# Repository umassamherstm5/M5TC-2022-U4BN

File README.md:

# M5TC-2022-U4BN
M5TC board that uses button inputs to display binary, decimal, and hexadecimal representations of unsigned 4-bit numbers.

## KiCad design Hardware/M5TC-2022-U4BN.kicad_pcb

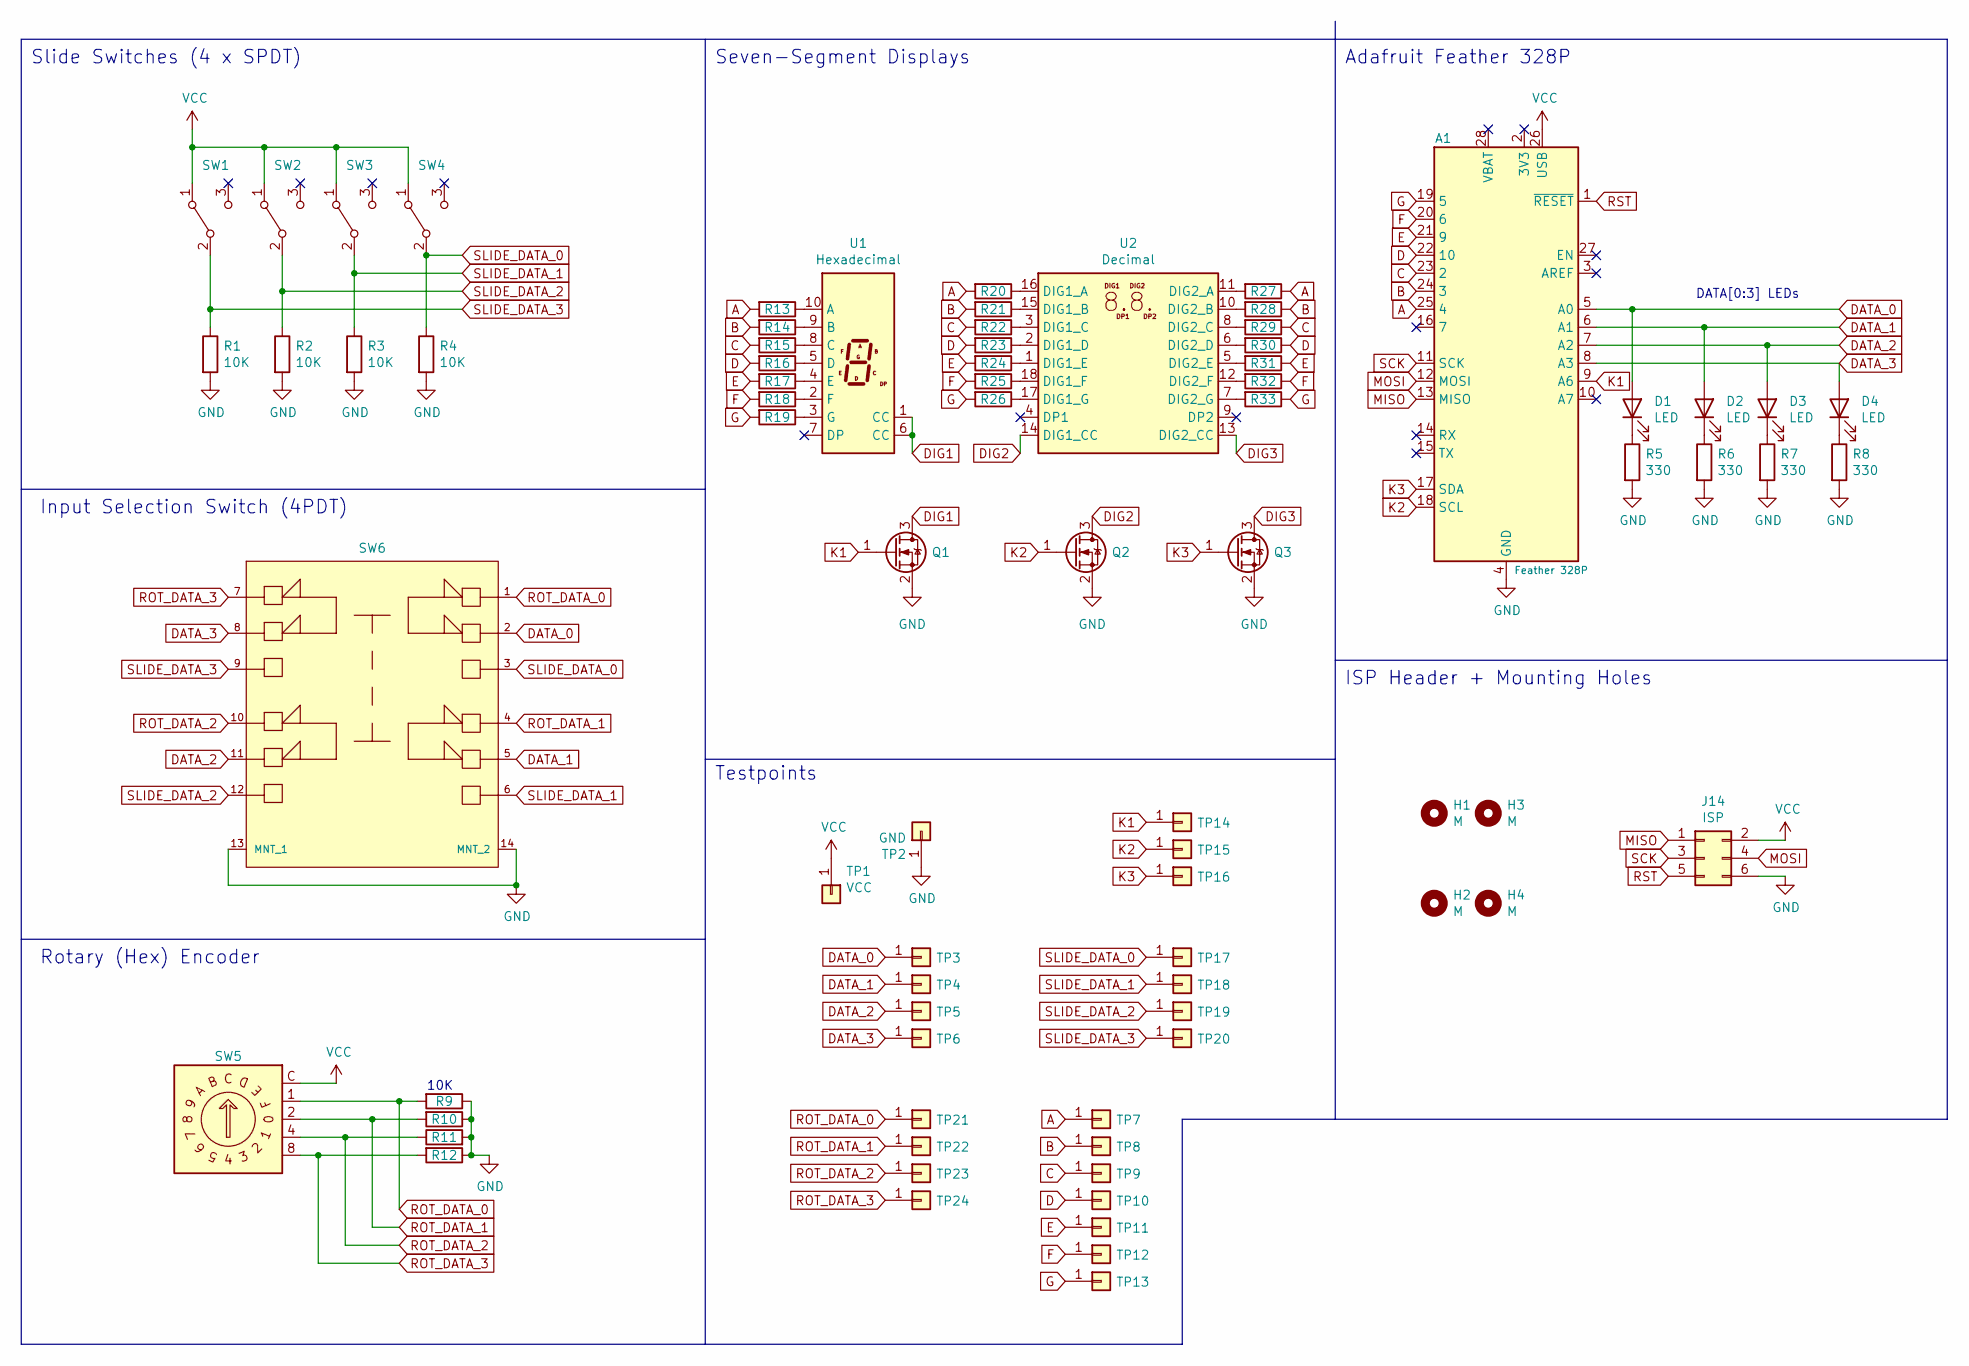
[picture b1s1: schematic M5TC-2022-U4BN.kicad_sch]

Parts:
A1: Feather 328P; Adafruit_Feather
D1, D2, D3, D4: LED; LED_D5.0mm
H1, H2, H3, H4: M; MountingHole_5.3mm_M5_Pad_Via
J14: ISP; PinSocket_2x03_P2.54mm_Vertical
Q1, Q2, Q3: 2N7002; SOT-23
R1, R2, R3, R4, R9, R10, R11, R12: 10K; R_1206_3216Metric
R5, R6, R7, R8, R13, R14, R15, R16, R17, R18, R19, R20, R21, R22, R23, R24, R25, R26, R27, R28, R29, R30, R31, R32, R33: 330; R_1206_3216Metric
SW1, SW2, SW3, SW4: SW_SPDT; E-Switch-EG1218
SW5: SW_Coded_SH-7050; Rotary_Hex_6_SOIC
SW6: EG4208A; E-Switch-EG4208A-0-0-MFG; mouser part number 612-EG4208A; digikey description SWITCH SLIDE 4PDT 200MA 30V
TP1: VCC; TestPoint_LoopPostPad
TP2: GND; TestPoint_LoopPostPad
TP3: DATA_0; TestPoint_LoopPostPad
TP4: DATA_1; TestPoint_LoopPostPad
TP5: DATA_2; TestPoint_LoopPostPad
TP6: DATA_3; TestPoint_LoopPostPad
TP7, TP8, TP9, TP10, TP11, TP12, TP13: Conn_01x01; TestPoint_LoopPost
TP14: K1; TestPoint_LoopPostPad
TP15: K2; TestPoint_LoopPostPad
TP16: K3; TestPoint_LoopPostPad
TP17: SLIDE_DATA_0; TestPoint_LoopPostPad
TP18: SLIDE_DATA_1; TestPoint_LoopPostPad
TP19: SLIDE_DATA_2; TestPoint_LoopPostPad
TP20: SLIDE_DATA_3; TestPoint_LoopPostPad
TP21: ROT_DATA_0; TestPoint_LoopPostPad
TP22: ROT_DATA_1; TestPoint_LoopPostPad
TP23: ROT_DATA_2; TestPoint_LoopPostPad
TP24: ROT_DATA_3; TestPoint_LoopPostPad
U1: Hexadecimal; HDSP-A151
U2: Decimal; DA56-11SURKWA

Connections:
A: A1.25 (4), R13.2, R20.2, R27.1, TP7.1
B: A1.24 (3), R14.2, R21.2, R28.1, TP8.1
C: A1.23 (2), R15.2, R22.2, R29.1, TP9.1
D: A1.22 (10), R16.2, R23.2, R30.1, TP10.1
DATA_0: A1.5 (A0), D1.2 (A), SW6.2, TP3.1
DATA_1: A1.6 (A1), D2.2 (A), SW6.5, TP4.1
DATA_2: A1.7 (A2), D3.2 (A), SW6.11, TP5.1
DATA_3: A1.8 (A3), D4.2 (A), SW6.8, TP6.1
DIG1: Q1.3 (D), U1.1 (CC), U1.6 (CC)
DIG2: Q2.3 (D), U2.14 (DIG1_CC)
DIG3: Q3.3 (D), U2.13 (DIG2_CC)
E: A1.21 (9), R17.2, R24.2, R31.1, TP11.1
F: A1.20 (6), R18.2, R25.2, R32.1, TP12.1
G: A1.19 (5), R19.2, R26.2, R33.1, TP13.1
GND: A1.4 (GND), J14.6, Q1.2 (S), Q2.2 (S), Q3.2 (S), R1.2, R2.2, R3.2, R4.2, R5.2, R6.2, R7.2, R8.2, R9.1, R10.1, R11.2, R12.1, SW6.13 (MNT_1), SW6.14 (MNT_2), TP2.1
K1: A1.9 (A6), Q1.1 (G), TP14.1
K2: A1.18 (SCL), Q2.1 (G), TP15.1
K3: A1.17 (SDA), Q3.1 (G), TP16.1
MISO: A1.13 (MISO), J14.1
MOSI: A1.12 (MOSI), J14.4
unnamed: D1.1 (K), R5.1
unnamed: D2.1 (K), R6.1
unnamed: D3.1 (K), R7.1
unnamed: D4.1 (K), R8.1
unnamed: R13.1, U1.10 (A)
unnamed: R14.1, U1.9 (B)
unnamed: R15.1, U1.8 (C)
unnamed: R16.1, U1.5 (D)
unnamed: R17.1, U1.4 (E)
unnamed: R18.1, U1.2 (F)
unnamed: R19.1, U1.3 (G)
unnamed: R20.1, U2.16 (DIG1_A)
unnamed: R21.1, U2.15 (DIG1_B)
unnamed: R22.1, U2.3 (DIG1_C)
unnamed: R23.1, U2.2 (DIG1_D)
unnamed: R24.1, U2.1 (DIG1_E)
unnamed: R25.1, U2.18 (DIG1_F)
unnamed: R26.1, U2.17 (DIG1_G)
unnamed: R27.2, U2.11 (DIG2_A)
unnamed: R28.2, U2.10 (DIG2_B)
unnamed: R29.2, U2.8 (DIG2_C)
unnamed: R30.2, U2.6 (DIG2_D)
unnamed: R31.2, U2.5 (DIG2_E)
unnamed: R32.2, U2.12 (DIG2_F)
unnamed: R33.2, U2.7 (DIG2_G)
ROT_DATA_0: R9.2, SW5.1, SW6.1, TP21.1
ROT_DATA_1: R10.2, SW5.2, SW6.4, TP22.1
ROT_DATA_2: R11.1, SW5.4, SW6.10, TP23.1
ROT_DATA_3: R12.2, SW5.8, SW6.7, TP24.1
RST: A1.1 (~RESET), J14.5
SCK: A1.11 (SCK), J14.3
SLIDE_DATA_0: R4.1, SW4.2 (B), SW6.3, TP17.1
SLIDE_DATA_1: R3.1, SW3.2 (B), SW6.6, TP18.1
SLIDE_DATA_2: R2.1, SW2.2 (B), SW6.12, TP19.1
SLIDE_DATA_3: R1.1, SW1.2 (B), SW6.9, TP20.1
VCC: A1.26 (USB), J14.2, SW1.1 (A), SW2.1 (A), SW3.1 (A), SW4.1 (A), SW5.C, TP1.1

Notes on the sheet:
Seven-Segment Displays
DATA[0:3] LEDs
Adafruit Feather 328P
Rotary (Hex) Encoder
10K
Slide Switches (4 x SPDT)
Input Selection Switch (4PDT)
Testpoints
ISP Header + Mounting Holes

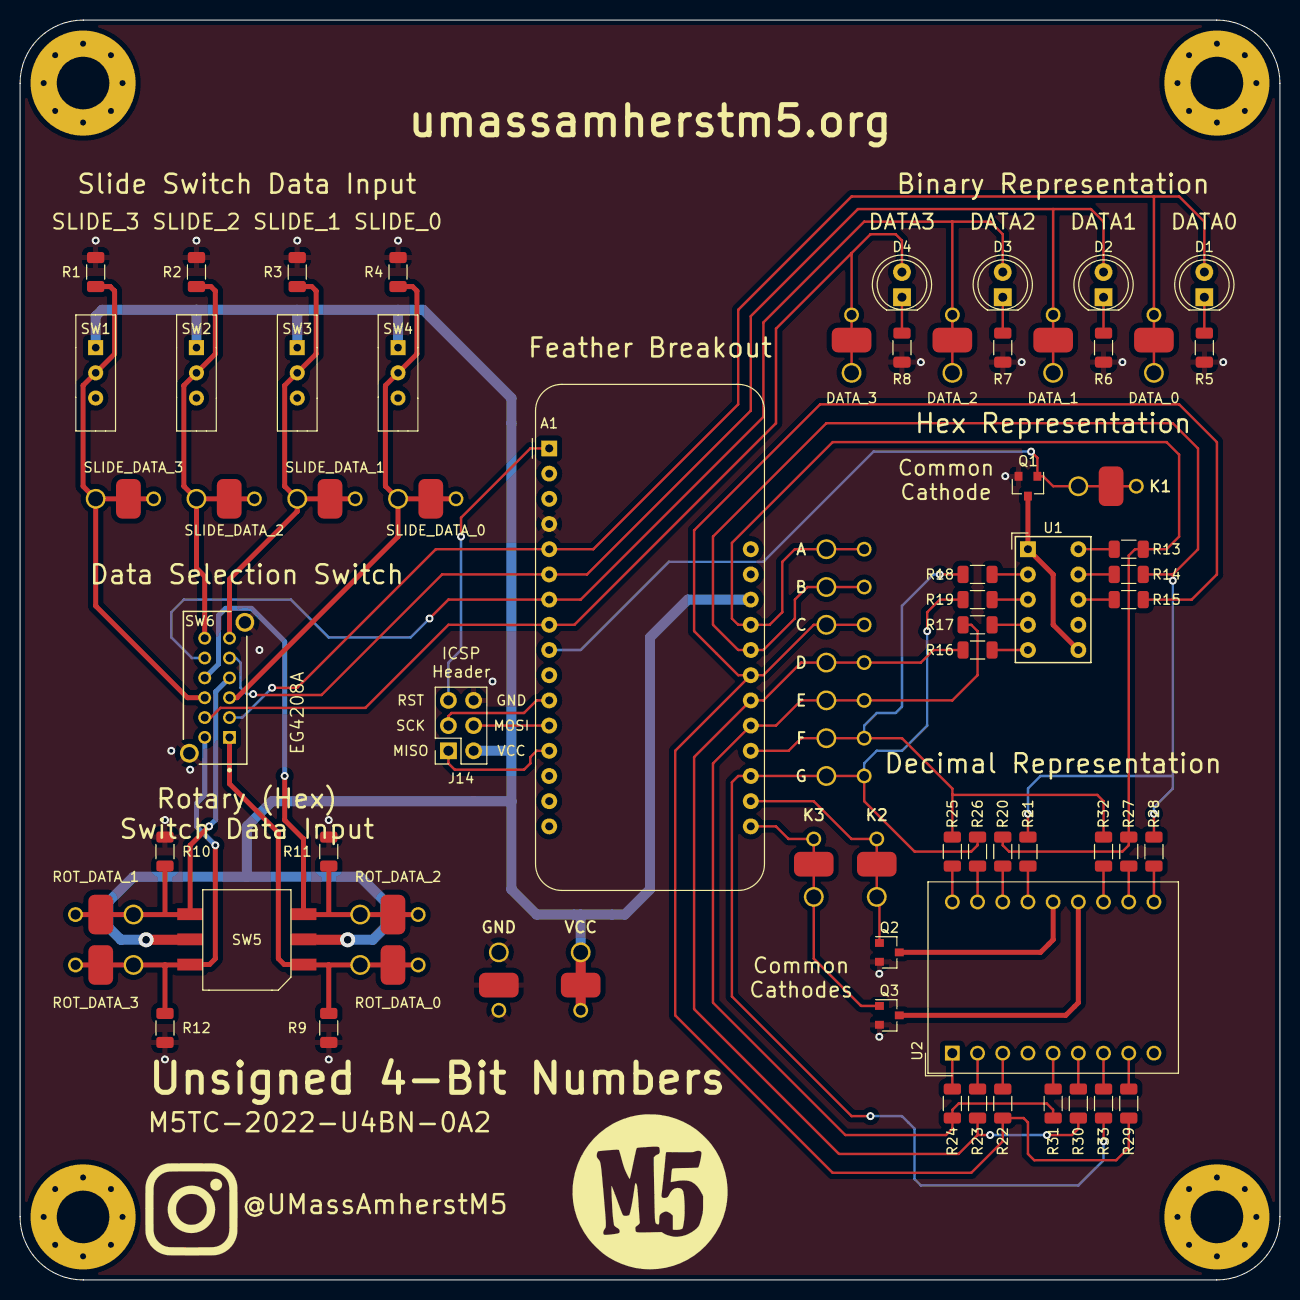
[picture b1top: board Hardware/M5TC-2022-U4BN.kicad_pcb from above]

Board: 2 copper layers, 127.0 x 127.0 mm, 78 parts (0 on the bottom side), 56 nets.

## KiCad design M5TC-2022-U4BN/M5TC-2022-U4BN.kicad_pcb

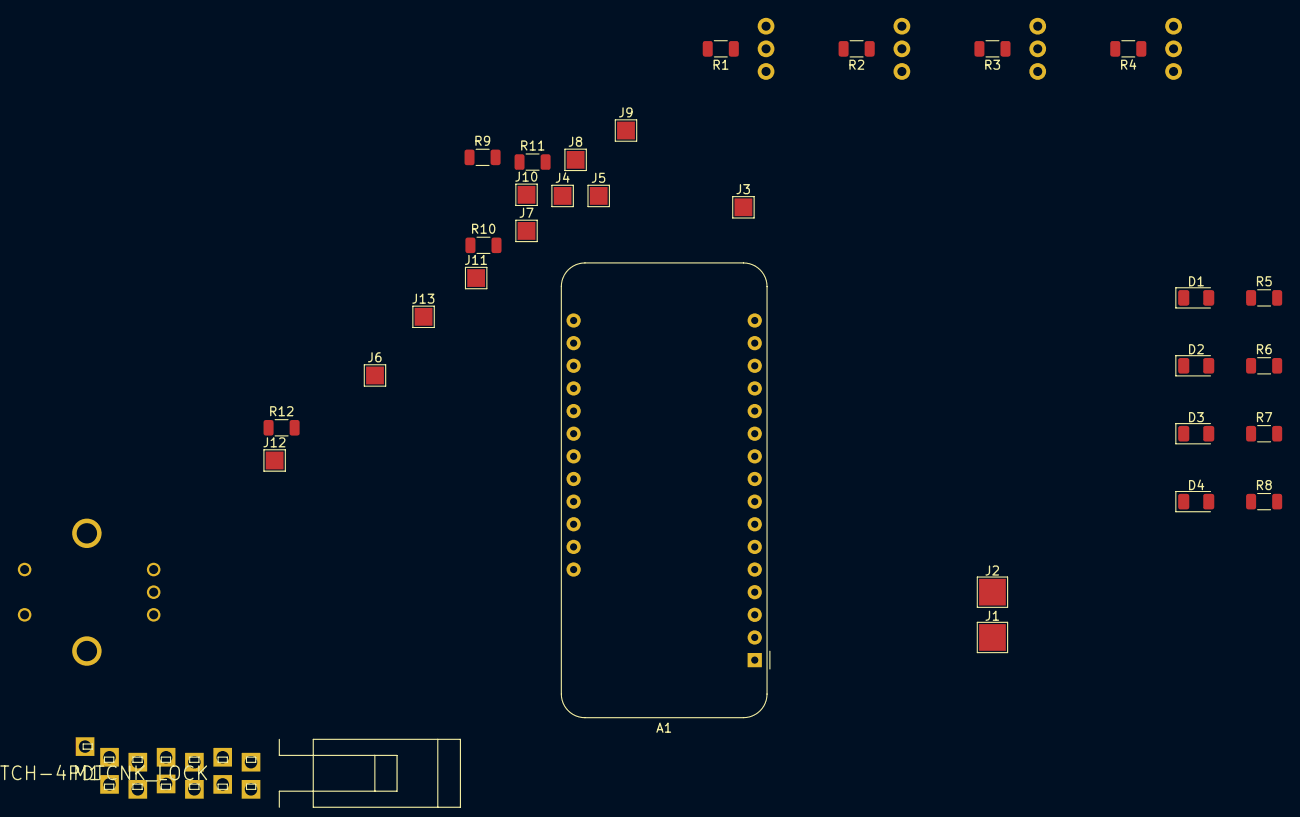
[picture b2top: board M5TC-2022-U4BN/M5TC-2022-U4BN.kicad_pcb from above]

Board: 2 copper layers, 36 parts (0 on the bottom side), 21 nets, no tracks yet.

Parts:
A1: Feather 328P; Adafruit_Feather
D1, D2, D3, D4: LED; LED_1206_3216Metric
J1: VCC; TestPoint_Pad_3.0x3.0mm
J2: GND; TestPoint_Pad_3.0x3.0mm
J3: DATA_0; TestPoint_Pad_2.0x2.0mm
J4: DATA_1; TestPoint_Pad_2.0x2.0mm
J5: DATA_2; TestPoint_Pad_2.0x2.0mm
J6: DATA_3; TestPoint_Pad_2.0x2.0mm
J7: K1; TestPoint_Pad_2.0x2.0mm
J8: K2; TestPoint_Pad_2.0x2.0mm
J9: K3; TestPoint_Pad_2.0x2.0mm
J10: SLIDE_DATA_0; TestPoint_Pad_2.0x2.0mm
J11: SLIDE_DATA_1; TestPoint_Pad_2.0x2.0mm
J12: SLIDE_DATA_2; TestPoint_Pad_2.0x2.0mm
J13: SLIDE_DATA_3; TestPoint_Pad_2.0x2.0mm
M1: SWITCH-4PDTCNK_LOCK; SWITCH-4PDT-CNK
R1, R2, R3, R4: 10K; R_1206_3216Metric
R5, R6, R7, R8: 330; R_1206_3216Metric
R9, R10, R11, R12: R; R_1206_3216Metric
SW1, SW2, SW3, SW4: SW_SPDT; SWITCH-SPDT
SW5: SW_Coded_SH-7050; ROTARY_ENC_PLAIN

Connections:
+5V: A1.26, SW1.1, SW2.1, SW3.1, SW4.1
DATA_0: A1.8, D1.2, J3.1, M1.PP$2
DATA_1: A1.7, D2.2, J4.1, M1.PP$5
DATA_2: A1.6, D3.2, J5.1, M1.PP$8
DATA_3: A1.5, D4.2, J6.1
GND: A1.4, J2.1, R1.2, R2.2, R3.2, R4.2, R5.2, R6.2, R7.2, R8.2, R9.1, R10.1, R11.2, R12.1
K1: A1.11, J7.1
K2: A1.12, J8.1
K3: A1.13, J9.1
unnamed: D1.1, R5.1
unnamed: D2.1, R6.1
unnamed: D3.1, R7.1
unnamed: D4.1, R8.1
ROT_DATA_0: M1.PP$3, R9.2
ROT_DATA_1: M1.PP$6, R10.2
ROT_DATA_2: M1.PP$9, R11.1
SLIDE_DATA_0: J10.1, M1.PP$1, R4.1, SW4.2
SLIDE_DATA_1: J11.1, M1.PP$4, R3.1, SW3.2
SLIDE_DATA_2: J12.1, M1.PP$7, R2.1, SW2.2
SLIDE_DATA_3: J13.1, R1.1, SW1.2
VCC: J1.1, SW5.C

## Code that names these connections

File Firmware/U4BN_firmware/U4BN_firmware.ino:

/*
 * M5TC-U4BN-0A2
 * -------------
 * Displays inputs from SDPT switch/rotary encoder as unsigned 4-bit numbers.
 * Authors: Akshat Sahay, Samridh Tuteja
 */

/*
 * Special Registers: 
 * ------------------
 * This code uses registers on the ATMEGA328P directly using AVR-C. 
 * Good reference: https://exploreembedded.com/wiki/Basics_of_AVR_%27C%27
 * Another good reference: https://www.youtube.com/watch?v=tBq3sO1Z-7o
 * 
 * We use registers directly TODO:{B/C it is better then teh arduino library sine it does not hide how the hardware works}. 
 * 
 * The 328P has 3 port registers: PORTB, PORTC and PORTD. 
 * We access them to get inputs and send outputs using the MCU. 
 * 
 * DDRx:
 * -----
 *  - Stands for Data Direction Register. 
 *  - Determines whether the pins on the specified port are inputs(0) or outputs(1). 
 *  - For example: DDRD = 00001100, here all pins except pins 2 and 3 are inputs on PORTD. 
 *  - Corresponding Arduino function: pinMode(); 
 * 
 * PORTx:
 * ------
 *  - Physical port on the ATMEGA328P. 
 *  - Determines whether the pins on the specified port are set HIGH(5V) or LOW(0V) in our code. 
 *  - For example: PORTB = 01100010, here we set all pins except pins 2, 5 and 6 are LOW. 
 *  - Corresponding Arduino function: digitalWrite(); 
 *  
 * PINx:
 * ------
 *  - Physical port on the ATMEGA328P. 
 *  - Checks the value of pins, either HIGH(5V) or LOW(0V). 
 *  - For example: data_decimal = PINC, here we assign the values of PORTC to the variable data_decimal. 
 *  - Corresponding Arduino function: digitalRead(); 
 */

#define SEG_DELAY_MS 1

#define SEG_A PD4
#define SEG_B PD3
#define SEG_C PD2
#define SEG_D PB2
#define SEG_E PB1
#define SEG_F PD6
#define SEG_G PD5

#define DATA_0 PC0
#define DATA_1 PC1
#define DATA_2 PC2
#define DATA_3 PC3

#define K1 PC6
#define K2 PC4
#define K3 PC5

/* registers variables */
unsigned char num_displayed = 0;  // number displayed on the 7-segment  
unsigned char data_decimal = 0;   // data from PORTC in decimal 
unsigned char data_hex = 0;       // data from PORTC in hex, two digits each 

void setup() {
  // set PORTB and PORTD as OUTPUT 
  DDRB = 0xFF; 
  DDRD = 0xFF; 
  
  // set PORTC as INPUT + K1, K2, K3 as OUTPUT
  DDRC = (0 << K1) | (1 << K2) | (1 << K3);
}

void loop() {
  // get DATA inputs from PORTC, we only want lower 4 bits 
  data_decimal = PINC & 0b00001111; 

  // display output to K1
  number_to_seg(data_decimal);
  
  PORTC |= (1 << K1);
  delay(SEG_DELAY_MS);
  PORTC &= ~(1 << K1);
  clear_seg();

  // display output to K2
  number_to_seg(data_decimal % 10);
  
  PORTC |= (1 << K2);
  delay(SEG_DELAY_MS);
  PORTC &= ~(1 << K2);
  clear_seg();

  // display output to K3
  number_to_seg(data_decimal / 10);
  
  PORTC |= (1 << K3);
  delay(SEG_DELAY_MS);
  PORTC &= ~(1 << K3);
  clear_seg();
}

void clear_seg() {
  PORTB &= ~(1 << SEG_D)|(1 << SEG_E);
  PORTD &= ~(
       (1 << SEG_A)
      |(1 << SEG_B)
      |(1 << SEG_C)
      |(1 << SEG_F)
      |(1 << SEG_G)
  );
}

/* turn on seven-segment signals based on num  */
void number_to_seg(unsigned char num) {
  if (num == 0) {
    // SEG_A ON, SEG_B ON, SEG_C ON, SEG_D ON, SEG_E ON, SEG_F ON, SEG_G OFF
    PORTB = (1 << SEG_D) | (1 << SEG_E); 
    PORTD = (1 << SEG_A) | (1 << SEG_B) | (1 << SEG_C) | (1 << SEG_F); 
  }

  if (num == 1) {
    // SEG_A OFF, SEG_B ON, SEG_C ON, SEG_D OFF, SEG_E OFF, SEG_F OFF, SEG_G OFF
    PORTB = 0x00; 
    PORTD = (1 << SEG_B) | (1 << SEG_C); 
  }

  if (num == 2) {
    // SEG_A ON, SEG_B ON, SEG_C OFF, SEG_D ON, SEG_E ON, SEG_F OFF, SEG_G ON
    PORTB = (1 << SEG_D) | (1 << SEG_E); 
    PORTD = (1 << SEG_A) | (1 << SEG_B) | (1 << SEG_G); 
  }

  if (num == 3) { 
    // SEG_A ON, SEG_B ON, SEG_C ON, SEG_D ON, SEG_E OFF, SEG_F OFF, SEG_G ON
    PORTB = (1 << SEG_D); 
    PORTD = (1 << SEG_A) | (1 << SEG_B) | (1 << SEG_C) | (1 << SEG_G); 
  }

  if (num == 4) {
    // SEG_A OFF, SEG_B ON, SEG_C ON, SEG_D OFF, SEG_E OFF, SEG_F ON, SEG_G ON 
    PORTB = 0x00;
    PORTD = (1 << SEG_B) | (1 << SEG_C) | (1 << SEG_F) | (1 << SEG_G); 
  }

  if (num == 5) {
    // SEG_A ON, SEG_B OFF, SEG_C ON, SEG_D ON, SEG_E OFF, SEG_F ON, SEG_G ON
    PORTB = (1 << SEG_D); 
    PORTD = (1 << SEG_A) | (1 << SEG_C) | (1 << SEG_F) | (1 << SEG_G); 
  }

  if (num == 6) {
    // SEG_A ON, SEG_B OFF, SEG_C ON, SEG_D ON, SEG_E ON, SEG_F ON, SEG_G ON
    PORTB = (1 << SEG_D) | (1 << SEG_E); 
    PORTD = (1 << SEG_A) | (1 << SEG_C) | (1 << SEG_F) | (1 << SEG_G); 
  }

  if (num == 7) {
    // SEG_A ON, SEG_B ON, SEG_C ON, SEG_D OFF, SEG_E OFF, SEG_F OFF, SEG_G OFF
    PORTB = 0; 
    PORTD = (1 << SEG_A) | (1 << SEG_B) | (1 << SEG_C); 
  }

  if (num == 8) {
    // SEG_A ON, SEG_B ON, SEG_C ON, SEG_D ON, SEG_E ON, SEG_F ON, SEG_G ON
    PORTB = (1 << SEG_D) | (1 << SEG_E); 
    PORTD = (1 << SEG_A) | (1 << SEG_B) | (1 << SEG_C) | (1 << SEG_F) | (1 << SEG_G); 
  }

  if (num == 9) {
    // SEG_A ON, SEG_B ON, SEG_C ON, SEG_D ON, SEG_E OFF, SEG_F ON, SEG_G ON
    PORTB = (1 << SEG_D); 
    PORTD = (1 << SEG_A) | (1 << SEG_B) | (1 << SEG_C) | (1 << SEG_F) | (1 << SEG_G); 
  }

  if (num == 10) {
    // SEG_A ON, SEG_B ON, SEG_C ON, SEG_D OFF, SEG_E ON, SEG_F ON, SEG_G ON 
    PORTB = (1 << SEG_E); 
    PORTD = (1 << SEG_A) | (1 << SEG_B) | (1 << SEG_C) | (1 << SEG_F) | (1 << SEG_G); 
  }

  if (num == 11) {
    // SEG_A OFF, SEG_B OFF, SEG_C ON, SEG_D ON, SEG_E ON, SEG_F ON, SEG_G ON
    PORTB = (1 << SEG_D) | (1 << SEG_E); 
    PORTD = (1 << SEG_C) | (1 << SEG_F) | (1 << SEG_G); 
  }

  if (num == 12) {
    // SEG_A ON, SEG_B OFF, SEG_C OFF, SEG_D ON, SEG_E ON, SEG_F ON, SEG_G OFF
    PORTB = (1 << SEG_D) | (1 << SEG_E); 
    PORTD = (1 << SEG_A) | (1 << SEG_F); 
  }

  if (num == 13) {
    // SEG_A OFF, SEG_B ON, SEG_C ON, SEG_D ON, SEG_E ON, SEG_F OFF, SEG_G ON
    PORTB = (1 << SEG_D) | (1 << SEG_E); 
    PORTD = (1 << SEG_B) | (1 << SEG_C) | (1 << SEG_G); 
  }

  if (num == 14) {
    // SEG_A ON, SEG_B OFF, SEG_C OFF, SEG_D ON, SEG_E ON, SEG_F ON, SEG_G ON
    PORTB = (1 << SEG_D) | (1 << SEG_E); 
    PORTD = (1 << SEG_A) | (1 << SEG_F) | (1 << SEG_G); 
  }

  if (num == 15) {
    // SEG_A ON, SEG_B OFF, SEG_C OFF, SEG_D OFF, SEG_E ON, SEG_F ON, SEG_G ON
    PORTB = (1 << SEG_E); 
    PORTD = (1 << SEG_A) | (1 << SEG_F) | (1 << SEG_G); 
  }
}

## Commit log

2022-03-02 Updated schematic
2022-03-22 Updated PCB, reorganized libraries
2022-03-25 Added triple test points
2022-10-27 Rerouted Board, Changed SOIC-Hex Size
2023-03-08 Updated software to clear segments

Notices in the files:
Hardware/M5TC-2022-U4BN.kicad_pcb:
License: CC BY 4.0
